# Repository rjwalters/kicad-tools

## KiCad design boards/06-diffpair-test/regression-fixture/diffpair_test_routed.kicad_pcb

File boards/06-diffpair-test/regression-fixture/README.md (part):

> **Current assembled demo (revision C):** four real SN65LVDS1DR / SN65LVDS2DR
> links. See [assembled-demo/README.md](../assembled-demo/README.md) for the circuit,
> procurement and build instructions. `output/` contains that assembly.
> Historical synthetic USB/PCIe/MIPI regression artifacts are retained in
> `regression-fixture/`; the old recipe now defaults to `regression-output/`.
> The historical protocol discussion below describes that regression only.

# Differential Pair Test Board (Board 06)

Regression testbench for the differential-pair routing subsystem introduced
by Epic [#2556](https://github.com/2AMLogic/kicad-tools/issues/2556)
(Phases 1-3).  Demonstrates each protocol family the epic was scoped against
(USB 2.0, USB 3.0, PCIe Gen1, MIPI D-PHY) by routing one or more diff pairs
per protocol on a 4-layer JLCPCB tier-1 stackup.

**This is not a working device.**  The source connectors (USB-C, mini-PCIe
edge, FFC) drive synthetic sink footprints (QFN, QFP, BGA simulator).  The
board's purpose is to exercise every Phase 1-3 net-class feature on at least
one pair so future router/validate changes have an end-to-end witness on
disk.

> **Not native-DRC evidence.** The footprints in this fixture's `*.kicad_pcb`
> files use invented library names (e.g. `Connector_FFC:FFC_4P_0.5mm`,
> `Package_BGA:BGA-49_5.0x5.0mm_Layout7x7_P0.5mm`) that are not in the stock
> KiCad libraries, so pinned kicad-cli DRC reports `lib_footprint_issues` on
> them. This artifact is a router regression witness only and must never be
> committed as native DRC/ERC evidence; the stock-named `../output/` board is
> the evidence artifact. Do not suppress `lib_footprint_issues` to hide this.

## Quick Start

```bash
# One-command build (recommended)
kct build boards/06-diffpair-test

# Or run specific steps
kct build boards/06-diffpair-test --step schematic
kct build boards/06-diffpair-test --step pcb
kct build boards/06-diffpair-test --step route
kct build boards/06-diffpair-test --step verify

# Run DRC against the committed routed PCB
kct check boards/06-diffpair-test/output/diffpair_test_routed.kicad_pcb --mfr jlcpcb
```

## Stackup

4-layer JLCPCB tier-1:

| Layer index | KiCad name | Purpose                              |
|-------------|-----------|--------------------------------------|
| 0           | F.Cu      | Signal (escape + outer routing)      |
| 1           | In1.Cu    | GND plane (impedance reference)      |
| 2           | In2.Cu    | PWR plane (+3V3 / +1V8 / +1V2)       |
| 31          | B.Cu      | Signal (optional bottom escape)      |

This is what the Phase 3K impedance formulas
(`src/kicad_tools/router/diffpair_impedance.py`) were calibrated against.

## Protocol Scenarios

| Scenario   | Pairs | Speed         | Source -> Sink                       | Phase features exercised                                          |
|------------|-------|---------------|--------------------------------------|-------------------------------------------------------------------|
| USB 2.0    | 1     | 480 Mbps      | USB-C (J1) -> QFN-32 (U1)            | 1C clearance, 2E coupled, 2G continuity, 3K 90 Ohm diff           |
| USB 3.0    | 4     | 5 Gbps        | USB-C (J1) -> BGA-49 simulator (U2)  | 1C, 2E, 2F BGA escape, 2G tight (0.9), 3K 90 Ohm, 3H 4.0 ps skew  |
| PCIe Gen1  | 2     | 2.5 Gbps      | Mini-PCIe edge (J3) -> QFP-48 (U3)   | 1C, 2E, 3H 8.1 ps skew, 3I serpentine, 3J skew DRC, 3K 100 Ohm    |
| MIPI D-PHY | 2     | 1 Gbps/lane   | FFC (J4) -> QFN-24 (U4)              | 1C, 2E, 3I serpentine (20.1 ps skew), 3K 100 Ohm                  |

**9 differential pairs / 18 paired nets**.  Combined with ground / power /
single-ended sideband (USB_CC1, USB_CC2, MIPI_RST), the board has **26 nets
total** --- comparable in scale to board 03 (13 nets) and well below
board 05 (~50 nets).

## Components

| Reference | Description                              | Footprint                                          |
|-----------|------------------------------------------|---------------------------------------------------|
| J1        | USB-C receptacle (USB 2.0 + USB 3.0)     | `Connector_USB:USB_C_Receptacle_USB2.0`           |
| J3        | Mini-PCIe card-edge (synthetic)          | `Connector_PCIE:PCIE_Mini_Edge`                   |
| J4        | 4-pin FFC, 0.5 mm pitch                  | `Connector_FFC:FFC_4P_0.5mm`                      |
| U1        | QFN-32, 0.5 mm pitch (USB 2.0 sink)      | `Package_DFN_QFN:QFN-32-1EP_5x5mm_P0.5mm`         |
| U2        | BGA-49 simulator, 0.5 mm pitch           | `Package_BGA:BGA-49_5.0x5.0mm_Layout7x7_P0.5mm`   |
| U3        | QFP-48, 0.5 mm pitch (PCIe sink)         | `Package_QFP:LQFP-48_7x7mm_P0.5mm`                |
| U4        | QFN-24, 0.5 mm pitch (MIPI sink)         | `Package_DFN_QFN:QFN-24-1EP_4x4mm_P0.5mm`         |

All sinks are placed on F.Cu so all routing happens on the outer signal
layers; GND/PWR planes are unencumbered for impedance reference.

## Per-Protocol Net Class Declarations

The protocol-specific `NetClassRouting` instances live in `generate_design.py`:

- `usb2_net_class()` --- `target_diff_impedance=90`, `intra_pair_clearance=0.075`, `pair_protocol="USB2_HS"`
- `usb3_net_class()` --- `target_diff_impedance=90`, `coupled_continuity_threshold=0.9`, `pair_protocol="USB3_SS"`
- `pcie_net_class()` --- `target_diff_impedance=100`, `pair_protocol="PCIE_G1"`
- `mipi_net_class()` --- `target_diff_impedance=100`, `pair_protocol="MIPI_DPHY"`, `data_rate_gbps=1.0`
- `sideband_net_class()` --- `target_single_impedance=50` (for USB_CC1/CC2, MIPI_RST)

No class sets `skew_tolerance_mm` (Issue #7894): every pair is held to the
derived ps skew budget of its declared protocol
([guide 09](../../../docs/guides/diff-pairs/09-skew-budget.md)).  USB 2.0,
USB 3.0 and PCIe Gen1 run at their protocol's maximum rate, so their budgets
are warnings; MIPI declares its 1 Gb/s lane rate, so its 20.1 ps budget is an
error.

`build_net_class_map()` assembles them into a `net_name -> NetClassRouting`
dict that both the autorouter (in `route_pcb()`) and the regression test
(`tests/test_board_06_diffpair_test.py::test_phase_features_exercised`)
import.  This ensures test-implementation parity.

## Files

| File                                          | Description                                          |
|-----------------------------------------------|------------------------------------------------------|
| `project.kct`                                 | KCT v1.0 spec (manufacturing/intent metadata)        |
| `generate_schematic.py`                       | Emits the schematic (`output/diffpair_test.kicad_sch`) |
| `generate_pcb.py`                             | Emits the unrouted PCB + holds the NETS / DIFFPAIRS dicts |
| `generate_design.py`                          | End-to-end pipeline (schematic + PCB + route + DRC)  |
| `output/diffpair_test.kicad_sch`              | Generated schematic (committed)                      |
| `output/diffpair_test.kicad_pcb`              | Unrouted PCB (committed)                             |
| `output/diffpair_test_routed.kicad_pcb`       | Routed PCB (committed --- consumed by CI DRC gate)   |

## DRC Status

The routed PCB is checked against JLCPCB tier-1 rules via:

```bash
kct check output/diffpair_test_routed.kicad_pcb --mfr jlcpcb --errors-only
```

**Phase-3 dependencies**:

- [#2649](https://github.com/2AMLogic/kicad-tools/issues/2649)
  (Phase 3J `diffpair_length_skew` DRC rule) --- **landed** in PR #2662.
  Once the router populates `skew_data`, the rule fires on PCIe / MIPI
  skew violations.
- [#2648](https://github.com/2AMLogic/kicad-tools/issues/2648)
  (Phase 3I serpentine insertion) --- **landed** (closed).  At
  scaffold-time it was still in progress, so PCIe / MIPI pairs could
  exceed their declared `skew_tolerance_mm` because the router couldn't
  yet meander to fix skew.

*Historical scaffold-time context*: per the Epic #2556 Phase 4L
mitigation strategy, this board was scaffolded with PCIe / MIPI pairs
declared but DRC tolerated at "non-strict" while #2648 was pending.
Both dependencies have since landed; the remaining tolerated residual is
the identity-keyed diff-pair quality block documented under "CI Gate"
below.

## Measuring Changes: Regen Determinism (#4536)

Full board-06 regeneration (`generate_design.py --step route`) was
run-to-run nondeterministic downstream of the coupled diff-pair
pre-phase --- two same-seed runs of unmodified `main` could differ by
thousands of lines ([#4536]).  Instrumented run matrices plus a CI-log
bisection localized **three** sources:

1. **Dominant: wall-clock truncation.**  The negotiated stage's
   `timeout=360.0` backstop straddled the phase's own natural runtime
   (363--367 s measured) and fired mid-iteration at a load-dependent net
   boundary in **every** run (different copper counts, 1599--1602
   segments), and any finite stage timeout also keeps the #3989
   remaining-budget per-net wall-clock caps active.  Fixed by removing
   wall-clock control flow from the negotiated stage (`timeout=None`;
   the stage is bounded by its deterministic iteration exits: per-net
   node-expansion budget, memory backstop, `max_iterations=3`,
   best-stall patience, and the #4463 zero-overflow fixed-point exit)
   and pinning `PYTHONHASHSEED=42` by construction at the
   `generate_design.py` entry point (one-shot re-exec), so plain
   invocations no longer depend on the caller exporting it.
   `max_iterations=3` is the *deterministic* replacement for what the
   backstop was doing: in every instrumented run (4 local baselines and
   the green CI run 31214686048) the 360 s cut landed at the very start
   of iteration 4, and iterations 4+ are provably discarded by the
   end-of-loop lex restore, so bounding the count reproduces the
   historical trajectory *and* saves the 9--14 minutes the discarded
   round cost.  Do not raise it back to the default 10 without
   re-measuring --- the board-06 E2E CI job ran to 29m45s of its 30-min
   ceiling with iteration 4 enabled.

2. **Reach-deciding: the relief rescue's 10 s sub-search wall clock.**
   Board-06 reach is decided at negotiated iteration 2 by ONE relief
   rescue (`MIPI_RST`), which rips four MIPI blockers and commits only
   if all four re-land (the no-net-loss transaction guarantee).  Those
   re-lands were bounded by a flat 10 s wall clock that straddles their
   8--12 s natural time on GitHub runners, so the same commit produced
   21/21 on one runner and 20/21 on another from routing logs that are
   line-identical up to the rescue.  Fixed with
   `route_all_negotiated(deterministic_rescue=True)`, which bounds the
   rescue's probe / re-land sub-searches by the deterministic per-net
   node-expansion cap instead.  This board opted in first (#4536) and
   remains an explicit opt-in: #4730 proposed making it the fleet default
   and withdrew the flip on a measured board-07 regression, so
   `DETERMINISTIC_RESCUE_DEFAULT` is `False` on every entry point.  The
   `True` here is therefore not documentary — it is **load-bearing for
   `REQUIRED_SIGNAL_REACH = 21`** in
   `scripts/ci/check_diffpair_coverage.py`.

3. **Residual: UUID-sorted file order.**  With the wall clock removed,
   runs produced byte-identical routing logs and identical copper
   *multisets* yet still ~2300 differing artifact lines.  Stage-snapshot
   comparison across two runs proved every stage through the repair-via
   placement identical, with divergence entering at the first post-repair
   `kct zones fill` --- `kicad-cli` re-saves the board with tracks
   ordered by UUID, and the stitch/pour-repair emitters minted random
   `uuid.uuid4()` values, so each run's refills sorted the *identical*
   copper into a different file order (isolation test: two fills of the
   same file are deterministic; a fill of a byte-equivalent file with
   different UUIDs reorders).  Fixed by minting deterministic UUIDs:
   content-derived uuid5 in `kct stitch` (`_stitch_uuid`) and
   sequence-derived uuid5 in this board's `_generate_uuid`.

**Determinism guard**: `tests/test_board06_determinism.py` runs two
consecutive same-seed shadow-OFF regens and asserts identical segment /
via counts, then byte-identity after normalizing uuid values (and
nothing else --- `kicad-cli` mints random uuid4s for the pads/properties
the generator emits without UUID fields, so raw byte identity can never
hold; all *copper* UUIDs are deterministic after #4536).  It costs two
full regens (~25 min), so it is skipped unless explicitly enabled:

```bash
KCT_BOARD06_DETERMINISM=1 uv run pytest tests/test_board06_determinism.py -v -s
```

**Scope-guard convention** (PR #4526 discussion): "flag-OFF run must
produce a byte-identical committed artifact" is decidable for board-06
again, with two provisos --- compare *uuid-normalized* text, and note
the committed artifact predates the #4536 fix, so regen-vs-committed
diffs remain expected until the artifact is next regenerated; the
run-to-run invariant (regen A vs regen B at the same commit) is the one
the test enforces.  Same-host runs only --- cross-host determinism is
#4561's axis, and shadow-ON determinism remains out of scope.  One more
proviso: run the two regens *sequentially on an otherwise-quiet host*
(the smoke test's own protocol).  Under extreme concurrent load
(measured at load-average ~90: parallel full test suites + mypy on the
same host) one of three post-fix runs flipped a single
stagnation-recovery reroute from success to failure and produced
different (valid) copper --- a resource-exhaustion sensitivity distinct
from the deterministic-logic sources fixed here (filed as #4724 with the
preserved evidence).

**The shadow-construction phase itself is fully deterministic.** This was
established independently more than once during a 5-issue diffpair sweep
(2026-08-03/04, [#4570]/[#4574]/[#4575]/[#4577]/[#4579]/[#4581]/[#4582]):
two full runs at the same commit produce byte-identical sets of all 33
`[coupled-tail]` lines, all 47 `[coupled-follow] declined` lines, and 323
gate rejections from the #4575 via-clearance gate (split 3+15+68+107+82+7+34+7
across the 9 pairs). The #4582 Judge independently reproduced the same
323 figure across four separate runs spanning both downstream modes
below. The nondeterminism is entirely downstream of this phase.

The **decline count is now 46**, not 47 --- [#4604] retired one decline.
Re-confirmed 2026-08-14 under [#4800] at 46 declines / 33 `[coupled-tail]`
lines on two independent runs, so use 46 as the baseline any new
measurement is compared against.

Reproduce the shadow phase and its debug trace:

```bash
KCT_BOARD06_SHADOW=1 PYTHONHASHSEED=42 uv run python \
  boards/06-diffpair-test/generate_design.py --step route --seed 42
# KCT_SHADOW_DEBUG=1 adds the [coupled-tail] / [coupled-follow] instrumentation
```

### The two downstream modes

**All figures in this subsection are from the shadow-ON configuration
(`KCT_BOARD06_SHADOW=1`, the repro block above).  The default recipe
runs shadow-OFF** --- `ENABLE_COUPLED_SHADOW` reads `KCT_BOARD06_SHADOW`
with default `"0"` (`generate_design.py`, the #3508 block), which is what
the committed artifact and CI use.

Once shadow output feeds the negotiated `route_all_negotiated` pass, the
shadow-ON board settles into one of two stable modes rather than a
continuum:

| (shadow-ON) | DRC errors | `diffpair_clearance_intra` | reach |
|---|---|---|---|
| Mode A | 32 | 7 | 19 of 21 |
| Mode B | 35 | 19 | 18 of 21 |

Both [#4800] repeats (2026-08-14, main @ `fa18a25b`) landed in **Mode B**
and were byte-identical to each other modulo `(uuid …)` --- 424 uuid lines
changed, zero geometry lines --- so on the current tree a shadow-ON pair of
runs is not guaranteed to sample both modes.  Sample enough repeats to
*identify* your mode before comparing; do not assume a single run of each
side straddles them.

`coupled-ok` is 5/9 in both modes --- the shadow-ON convergence figure
recorded in the recipe comments ("Convergence is 5/9 (post-#4576)").  A
run's mode is identifiable from three mutually consistent signals ---
total DRC error count, the `diffpair_clearance_intra` count, and reach
--- which is what makes paired mode-for-mode comparison possible instead
of guesswork.

**If you ran with the default (shadow-OFF), you are not in either
mode.** Expect the CI seed-42 re-route instead: **11 blocking DRC
errors**, every one listed by identity in
`DIFFPAIR_FIXTURE_ALLOWED_FINDINGS` (`scripts/ci/check_diffpair_coverage.py`,
#7367: 9 `diffpair_length_skew` pairs, 1 `diffpair_uncoupled_length`,
1 `impedance`), at **21 of 21** reach --- the shadow-OFF reach recorded
in the same recipe comments.  A default-config run landing on those numbers is the expected
result, not an unrecognized third mode.

### Measurement convention

- **Compare shadow-phase counters directly.** The `[coupled-tail]` /
  `[coupled-follow] declined` line counts and the per-pair gate-rejection
  split are deterministic; a difference there is a real signal.
- **Compare full-regen (board-level) results paired mode-for-mode.**
  Identify each side's mode from the three signals above before
  comparing error counts, `diffpair_clearance_intra`, or reach across a
  change.
- **Never assert a delta from a single run of each side.** A lone
  before/after pair can silently compare Mode A against Mode B and
  report a mode flip as a regression or a win. Run enough repeats to
  identify the mode on both sides first.

Two traps this has already cost people:

1. A Builder's first baseline landed in Mode A while the Curator's had
   landed in Mode B, so the two disagreed on the "current" numbers and
   neither was wrong.
2. A Builder ran a narrow-vs-broad comparison that looked decisive and
   was pure mode noise --- only paired sampling separated signal from
   [#4536].

### Standing invariants and the vacuity trap

A change should not drop `coupled-ok` below 5/9, and should not drop
reach when compared mode-for-mode.  **The 5/9 figure is the shadow-ON
convergence number** recorded in the recipe comments next to
`ENABLE_COUPLED_SHADOW`; like the mode table, it is an invariant for
shadow-ON runs, so evaluate it against a shadow-ON baseline rather than
a default (shadow-OFF) one.  Watch for the **vacuity trap**:
`diffpair_length_skew` only fires on an *engaged* (coupled) pair, so a
change that knocks a pair from coupled to declined removes it from
skew-checking entirely --- the error count can drop while the change is
a regression, not a win.  Always read `coupled-ok` and reach alongside
the raw error count, never the error count alone.

### Why the default is shadow-OFF (measured, [#4800], 2026-08-14)

The obvious question --- "5/9 coupled beats 0/9, why is this off?" --- has
a measured answer.  Two repeats per arm on main @ `fa18a25b`
(`PYTHONHASHSEED=42 … --seed 42`, C++ backend built), board quality read
with the CI gate itself (`scripts/ci/check_diffpair_coverage.py
--skip-route`) and cross-checked with `kicad-cli pcb drc --refill-zones`:

| | shadow OFF (default) | shadow ON |
|---|---|---|
| `coupled-ok` | 0/9 | 5/9 |
| `[coupled-follow] declined` | n/a | 46 |
| signal reach | **21/21** | **18/21** |
| `kct check` DRC errors | **18** (allowlist 18) | **35** |
| diff-pair violations | 18 (baseline 18) | 31 |
| pour connectivity | PASS | **FAIL** (+3V3 3 groups, GND 5 groups) |
| `kicad-cli` errors | 444 (11 clearance) | 639–646 (169–176 clearance) |
| `kicad-cli` unconnected | 0 | **9** |
| `--step route` wall-clock | 745.2 s / 739.9 s | 1649.8 s / 1570.6 s |
| CI gate exit code | **0** | **2** (4 assertions) |

The 5 pairs that couple are stable by name --- MIPI_CLK, PCIE_RX, USB2_D,
USB3_TX1, USB3_TX2.  The three stranded nets are MIPI_D0+, MIPI_D0- and
USB_CC1; the [#4463] corridor-yield recovery yields MIPI_CLK, re-runs,
measures `reach 18 -> 18 of 21` and **reverts**, so shadow-ON no longer
reaches the 19/21 recorded on 2026-08-02.  USB_CC1 is still not a
corridor-competition failure --- the planner says so itself:
`[corridor-yield] USB_CC1 stays unroutable with every coupled corridor
lifted`.  Wall-clock is 2.16x, against a CI job already running a median
24.5 min of its 30-minute ceiling (ten consecutive green main runs,
2026-08-14; the re-route step alone is 23m30s).

### The crossover legality census (`KCT_CROSSTAIL_CENSUS=1`)

The shadow constructor's crossover tails ship the **first** legal via-site
candidate out of a 225-entry lattice and report nothing about the rest, so an
*ordering* problem (many sites legal, a better key would pick a kinder one)
looks exactly like a *saturation* one (almost nothing is legal, so no key can
help).  `KCT_CROSSTAIL_CENSUS=1` ([#4580]) scans the whole lattice instead and
prints one header per crossover:

```bash
KCT_CROSSTAIL_CENSUS=1 KCT_BOARD06_SHADOW=1 PYTHONHASHSEED=42 uv run python \
  boards/06-diffpair-test/generate_design.py --step route --seed 42
# [crosstail-census] net=… head=(…) goal=(…) legal=2/225 distinct_v1=1 census_s=0.0164
```

`distinct_v1` is the field that separates the two worlds: a legal set that is a
singleton in `v1` carries the same barrel on every legal route, so no ordering
key can move the result and the constraint lives upstream in placement / escape
planning.

Add `KCT_CROSSTAIL_CENSUS_REPORT=<path>`
([#4799](https://github.com/2AMLogic/kicad-tools/issues/4799)) to get the same measurement
as **data** instead of scraped stdout: a JSON document with one record per
crossover plus the aggregate the per-crossover headers cannot give you
(`saturated_pct`, `no_ordering_lever_pct`, `inert_pct`, an advisory `verdict`).
The diff-pair phase also closes with a `[crosstail-census-summary]` block
whenever the census is on.  It is report-only and costs ~1 µs per crossover on
top of the census itself; schema and interpretation live in
[`docs/reference/crosstail-census-report.md`](../../../docs/reference/crosstail-census-report.md).

That report is a post-mortem, but it does not have to be read as one: feeding
it back in with `kct route --census-advisory <report.json>` (or
`KCT_CROSSTAIL_CENSUS_ADVISORY=<path>`) prints this board's saturation figure
**before** the next route's first A\* expansion, cross-checked against the
board's current nets and suppressed when the report is stale.  Advisory by
default — it cannot change or fail a route.  Adding `--census-advisory-gate`
(opt-in) turns that prediction into a go/no-go: on this board's own report it
exits **9** before any router work rather than spending the 28 minutes again,
naming the worst nets and pointing at placement / escape planning as the fix
layer.  A prediction that cannot be trusted (stale, `not-applicable`,
census-disabled) never gates.

**State-neutral is not the same as budget-neutral ([#4635]).** PR [#4611]'s
prose claimed the census "cannot" change the route because it is
"observation-only by construction".  That is true of router **state** — every
gate the scan calls past the accept point is mutation-free, so continuing the
sweep cannot perturb anything.  It was **not** true of the wall-clock
**budget**: the census runs inside the shadow phase's per-pair window, and every
downstream deadline there is computed as `<budget> - <elapsed since the window
opened>`, so census seconds were silently deducted from the probes that follow.
A census-on run could therefore differ from a census-off run through budget
pressure alone.  Since #4635 the census credits its own **incremental** cost
(the sweep after the first legal candidate — zero when nothing is legal, since
both modes then scan the whole lattice) back to that window, so census-on and
census-off runs get the same effective downstream budget.  The trade is
deliberate: a census-on pair's *true* wall clock may now exceed the 30 s
`_SHADOW_PER_PAIR_BUDGET_S` by the census's own cost, which stays visible in
`census_s=` and in the unadjusted per-pair `[coupled-timing] elapsed=` line.

**Measured on this board** (shadow-ON, seed 42, 2026-08-04 — re-measure before
quoting): 166 crossovers, of which **150 (90.4%) have `legal=0/225`** and so
credit exactly zero.  Total credited census time across the whole shadow phase
is **1.28 s**; the worst single pair (USB3_TX1) accrues **0.86 s**, i.e. under
3% of its 30 s budget.  That is a **refutation** of the budget-pressure
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
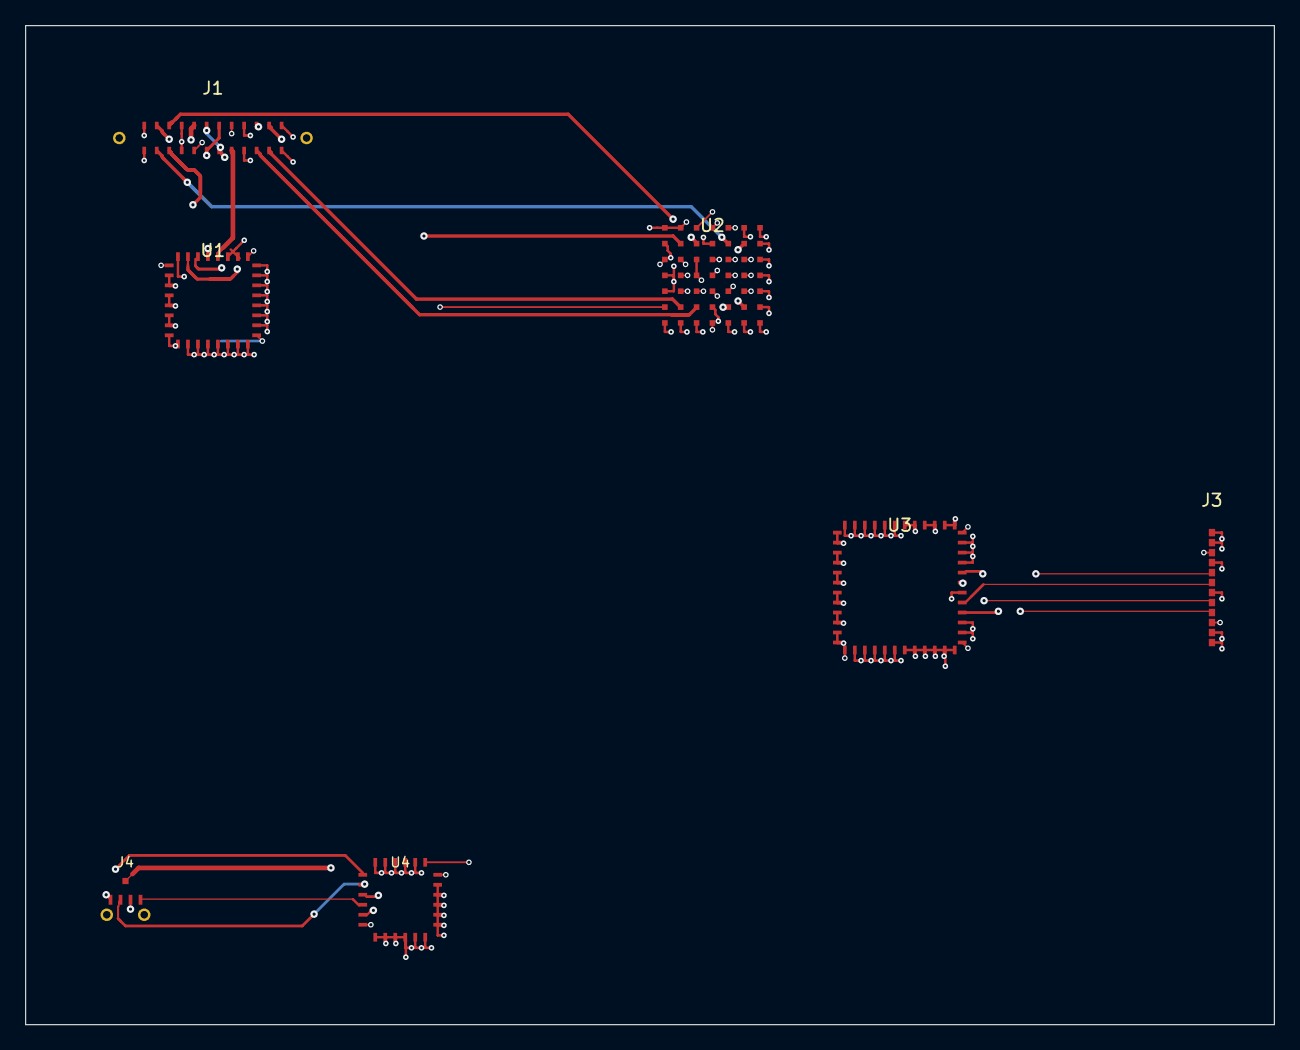
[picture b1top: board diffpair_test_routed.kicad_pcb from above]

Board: 4 copper layers, 100.0 x 80.0 mm, 7 parts (0 on the bottom side), 26 nets.

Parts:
J1: USB-C; USB_C_Receptacle_USB2.0
J3: MiniPCIe; PCIE_Mini_Edge
J4: FFC4; FFC_4P_0.5mm
U1: QFN32_USB2; QFN-32-1EP_5x5mm_P0.5mm
U2: BGA49_USB3; BGA-49_5.0x5.0mm_Layout7x7_P0.5mm
U3: QFP48_PCIe; LQFP-48_7x7mm_P0.5mm
U4: QFN24_MIPI; QFN-24-1EP_4x4mm_P0.5mm

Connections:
+1V2: J3.10, U2.C3, U2.C4, U2.C5, U2.D2, U2.D3, U2.D4, U2.D5, U2.D6, U2.E3, U2.E4, U2.E5, U3.36
+1V8: U1.16, U4.6, U4.18
+3V3: J1.A8, J1.B8, J3.3, U1.1, U1.17, U2.C2, U2.C6, U2.E2, U2.E6, U3.25, U4.12
GND: J1.A1, J1.A12, J1.B1, J1.B12, J1.S1, J1.S2, J3.1, J3.2, J3.4, J3.7, J3.11, J3.12, J4.M1, J4.M2, U1.2, U1.3, U1.4, U1.5, U1.6, U1.7, U1.8, U1.14, U1.15, U1.18, U1.19, U1.20, U1.21, U1.22, U1.23, U1.24, U1.25, U1.26, U1.27, U1.28, U1.29, U1.30, U1.31, U1.32, U2.A1, U2.A2, U2.A3, U2.A4, U2.A5, U2.A6, U2.A7, U2.B1, U2.B4, U2.B7, U2.C1, U2.C7, U2.D1, U2.D7, U2.E1, U2.E7, U2.F1, U2.F4, U2.F7, U2.G1, U2.G2, U2.G3, U2.G4, U2.G5, U2.G6, U2.G7, U3.1, U3.2, U3.3, U3.4, U3.5, U3.6, U3.7, U3.8, U3.9, U3.10, U3.11, U3.12, U3.13, U3.14, U3.15, U3.16, U3.17, U3.18, U3.19, U3.20, U3.21, U3.22, U3.23, U3.24, U3.26, U3.27, U3.30, U3.33, U3.34, U3.35, U3.37, U3.38, U3.39, U3.40, U3.41, U3.42, U3.43, U3.44, U3.45, U3.46, U3.47, U3.48, U4.7, U4.8, U4.9, U4.10, U4.11, U4.13, U4.14, U4.15, U4.16, U4.17, U4.19, U4.20, U4.21, U4.22, U4.23, U4.24
MIPI_CLK+: J4.1, U4.1
MIPI_CLK-: J4.2, U4.2
MIPI_D0+: J4.3, U4.3
MIPI_D0-: J4.4, U4.4
MIPI_RST: J4.RST, U4.5
PCIE_RX+: J3.8, U3.31
PCIE_RX-: J3.9, U3.32
PCIE_TX+: J3.5, U3.28
PCIE_TX-: J3.6, U3.29
USB2_D+: J1.A6, J1.B6, U1.10
USB2_D-: J1.A7, J1.B7, U1.11
USB3_RX1+: J1.B11, U2.B5
USB3_RX1-: J1.B10, U2.B6
USB3_RX2+: J1.A11, U2.F5
USB3_RX2-: J1.A10, U2.F6
USB3_TX1+: J1.A2, U2.B2
USB3_TX1-: J1.A3, U2.B3
USB3_TX2+: J1.B2, U2.F2
USB3_TX2-: J1.B3, U2.F3
USB_CC1: J1.A5, U1.12
USB_CC2: J1.B5, U1.13
VBUS_USB: J1.A4, J1.A9, J1.B4, J1.B9, U1.9

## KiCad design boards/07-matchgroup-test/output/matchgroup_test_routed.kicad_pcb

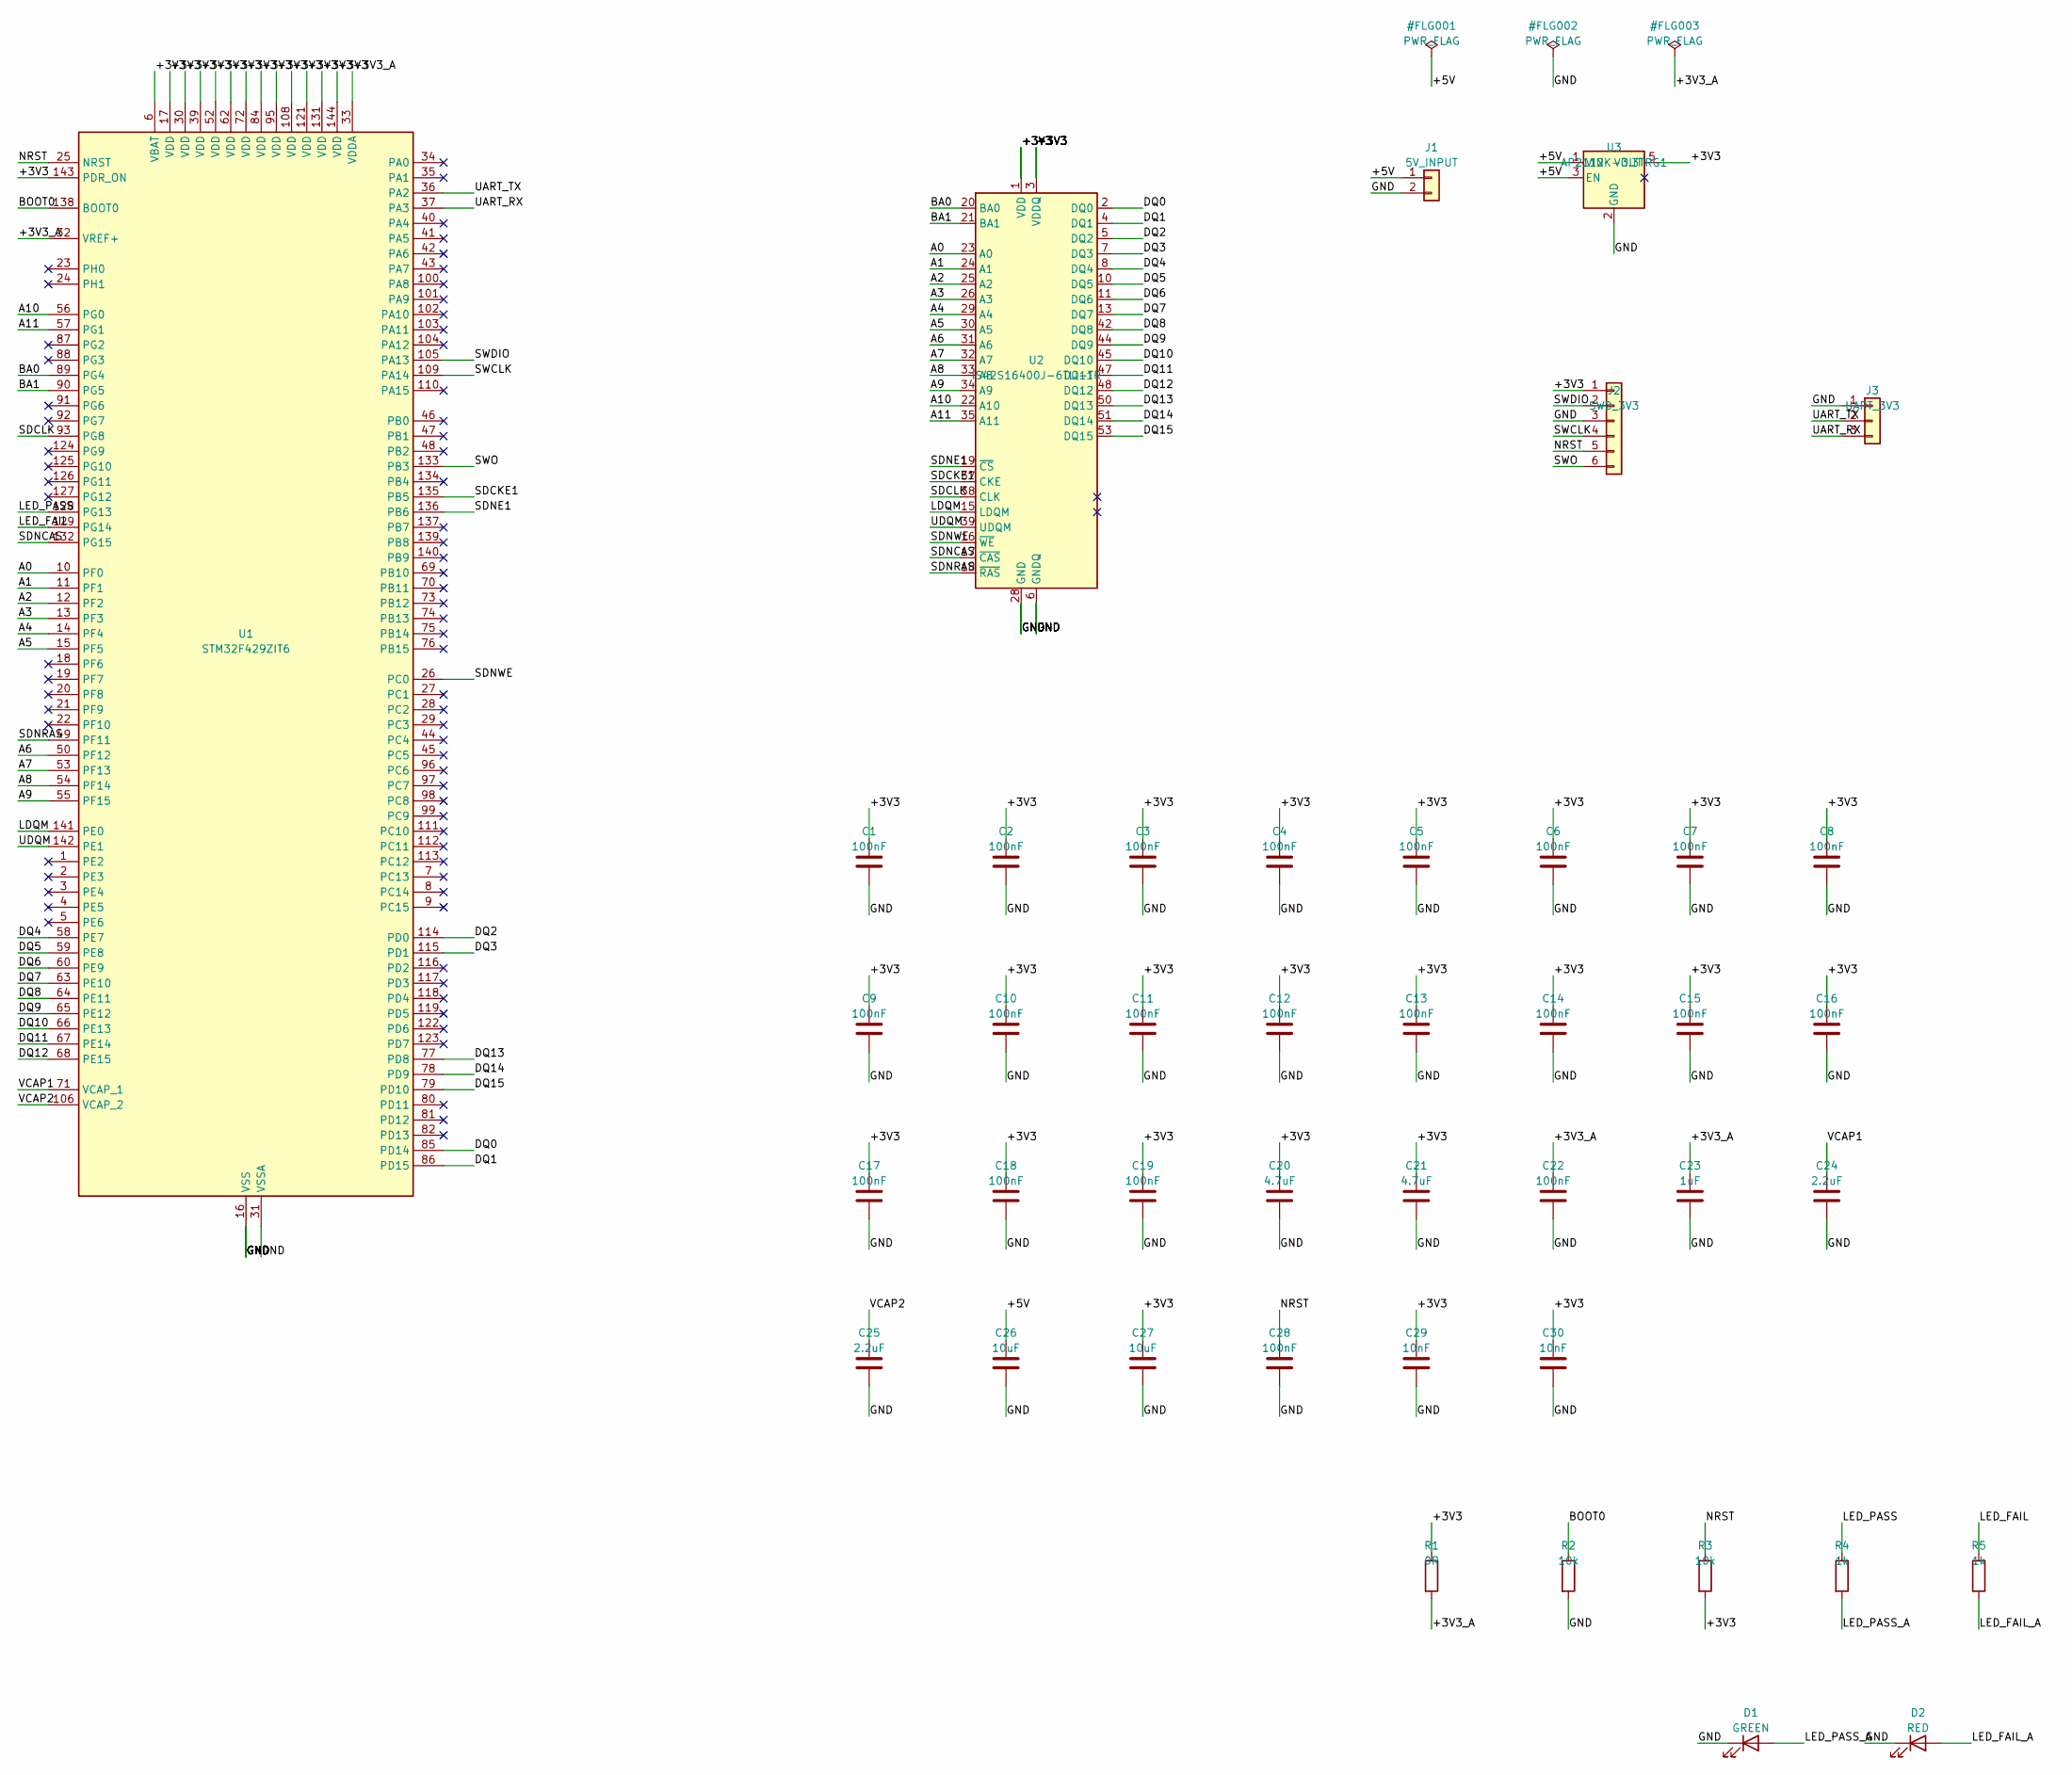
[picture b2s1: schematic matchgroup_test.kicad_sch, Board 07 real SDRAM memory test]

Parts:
C1, C2, C3, C4, C5, C6, C7, C8, C9, C10, C11, C12, C13, C14, C15, C16, C17, C18, C19, C22, C28: 100nF; C_0603_1608Metric; Manufacturer_Part_Number CC0603KRX7R9BB104; LCSC C14663
C20, C21: 4.7uF; C_0603_1608Metric; Manufacturer_Part_Number CL10A475KP8NNNC; LCSC C1705
C23: 1uF; C_0603_1608Metric; Manufacturer_Part_Number CL10A105KB8NNNC; LCSC C15849
C24, C25: 2.2uF; C_0603_1608Metric; Manufacturer_Part_Number CL10A225KO8NNNC; LCSC C23630
C26, C27: 10uF; C_0603_1608Metric; Manufacturer_Part_Number CL10A106KP8NNNC; LCSC C19702
C29, C30: 10nF; C_0603_1608Metric; Manufacturer_Part_Number CL10B103KB8NNNC; LCSC C1589
D1: GREEN; LED_0603_1608Metric; Manufacturer_Part_Number LTST-C190KGKT; LCSC C125094
D2: RED; LED_0603_1608Metric; Manufacturer_Part_Number LTST-C190KRKT; LCSC C94869
J1: 5V_INPUT; PinHeader_1x02_P2.54mm_Vertical; Manufacturer_Part_Number B-2100S02P-A110; LCSC C124375
J2: SWD_3V3; PinHeader_1x06_P2.54mm_Vertical; Manufacturer_Part_Number 2.54-1x6P; LCSC C37208
J3: UART_3V3; PinHeader_1x03_P2.54mm_Vertical; Manufacturer_Part_Number 2.54-1*3P; LCSC C49257
R1: 0R; R_0603_1608Metric; Manufacturer_Part_Number 0603WAF0000T5E; LCSC C21189
R2, R3: 10k; R_0603_1608Metric; Manufacturer_Part_Number 0603WAF1002T5E; LCSC C25804
R4, R5: 1k; R_0603_1608Metric; Manufacturer_Part_Number 0603WAF1001T5E; LCSC C21190
U1: STM32F429ZIT6; LQFP-144_20x20mm_P0.5mm; Manufacturer_Part_Number STM32F429ZIT6; LCSC C84808
U2: IS42S16400J-6TLI-TR; TSOP-II-54_22.2x10.16mm_P0.8mm; Manufacturer_Part_Number IS42S16400J-6TLI-TR; LCSC C17216754
U3: AP2112K-3.3TRG1; SOT-23-5; Manufacturer_Part_Number AP2112K-3.3TRG1; LCSC C51118

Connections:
+3V3: C1.1, C2.1, C3.1, C4.1, C5.1, C6.1, C7.1, C8.1, C9.1, C10.1, C11.1, C12.1, C13.1, C14.1, C15.1, C16.1, C17.1, C18.1, C19.1, C20.1, C21.1, C27.1, C29.1, C30.1, J2.1, R1.1, R3.2, U1.6 (VBAT), U1.17 (VDD), U1.30 (VDD), U1.39 (VDD), U1.52 (VDD), U1.62 (VDD), U1.72 (VDD), U1.84 (VDD), U1.95 (VDD), U1.108 (VDD), U1.121 (VDD), U1.131 (VDD), U1.143 (PDR_ON), U1.144 (VDD), U2.1 (VDD), U2.3 (VDDQ), U2.9 (VDDQ), U2.14 (VDD), U2.27 (VDD), U2.43 (VDDQ), U2.49 (VDDQ), U3.5 (VOUT)
+3V3_A: C22.1, C23.1, R1.2, U1.32 (VREF+), U1.33 (VDDA)
+5V: C26.1, J1.1, U3.1 (VIN), U3.3 (EN)
A0: U1.10 (PF0), U2.23 (A0)
A1: U1.11 (PF1), U2.24 (A1)
A2: U1.12 (PF2), U2.25 (A2)
A3: U1.13 (PF3), U2.26 (A3)
A4: U1.14 (PF4), U2.29 (A4)
A5: U1.15 (PF5), U2.30 (A5)
A6: U1.50 (PF12), U2.31 (A6)
A7: U1.53 (PF13), U2.32 (A7)
A8: U1.54 (PF14), U2.33 (A8)
A9: U1.55 (PF15), U2.34 (A9)
A10: U1.56 (PG0), U2.22 (A10)
A11: U1.57 (PG1), U2.35 (A11)
BA0: U1.89 (PG4), U2.20 (BA0)
BA1: U1.90 (PG5), U2.21 (BA1)
BOOT0: R2.1, U1.138 (BOOT0)
DQ0: U1.85 (PD14), U2.2 (DQ0)
DQ1: U1.86 (PD15), U2.4 (DQ1)
DQ2: U1.114 (PD0), U2.5 (DQ2)
DQ3: U1.115 (PD1), U2.7 (DQ3)
DQ4: U1.58 (PE7), U2.8 (DQ4)
DQ5: U1.59 (PE8), U2.10 (DQ5)
DQ6: U1.60 (PE9), U2.11 (DQ6)
DQ7: U1.63 (PE10), U2.13 (DQ7)
DQ8: U1.64 (PE11), U2.42 (DQ8)
DQ9: U1.65 (PE12), U2.44 (DQ9)
DQ10: U1.66 (PE13), U2.45 (DQ10)
DQ11: U1.67 (PE14), U2.47 (DQ11)
DQ12: U1.68 (PE15), U2.48 (DQ12)
DQ13: U1.77 (PD8), U2.50 (DQ13)
DQ14: U1.78 (PD9), U2.51 (DQ14)
DQ15: U1.79 (PD10), U2.53 (DQ15)
GND: C1.2, C2.2, C3.2, C4.2, C5.2, C6.2, C7.2, C8.2, C9.2, C10.2, C11.2, C12.2, C13.2, C14.2, C15.2, C16.2, C17.2, C18.2, C19.2, C20.2, C21.2, C22.2, C23.2, C24.2, C25.2, C26.2, C27.2, C28.2, C29.2, C30.2, D1.1 (K), D2.1 (K), J1.2, J2.3, J3.1, R2.2, U1.16 (VSS), U1.31 (VSSA), U1.38 (VSS), U1.51 (VSS), U1.61 (VSS), U1.83 (VSS), U1.94 (VSS), U1.107 (VSS), U1.120 (VSS), U1.130 (VSS), U2.6 (GNDQ), U2.12 (GNDQ), U2.28 (GND), U2.41 (GND), U2.46 (GNDQ), U2.52 (GNDQ), U2.54 (GND), U3.2 (GND)
LDQM: U1.141 (PE0), U2.15 (LDQM)
LED_FAIL: R5.1, U1.129 (PG14)
LED_FAIL_A: D2.2 (A), R5.2
LED_PASS: R4.1, U1.128 (PG13)
LED_PASS_A: D1.2 (A), R4.2
NRST: C28.1, J2.5, R3.1, U1.25 (NRST)
SDCKE1: U1.135 (PB5), U2.37 (CKE)
SDCLK: U1.93 (PG8), U2.38 (CLK)
SDNCAS: U1.132 (PG15), U2.17 (~CAS)
SDNE1: U1.136 (PB6), U2.19 (~CS)
SDNRAS: U1.49 (PF11), U2.18 (~RAS)
SDNWE: U1.26 (PC0), U2.16 (~WE)
SWCLK: J2.4, U1.109 (PA14)
SWDIO: J2.2, U1.105 (PA13)
SWO: J2.6, U1.133 (PB3)
UART_RX: J3.3, U1.37 (PA3)
UART_TX: J3.2, U1.36 (PA2)
UDQM: U1.142 (PE1), U2.39 (UDQM)
VCAP1: C24.1, U1.71 (VCAP_1)
VCAP2: C25.1, U1.106 (VCAP_2)

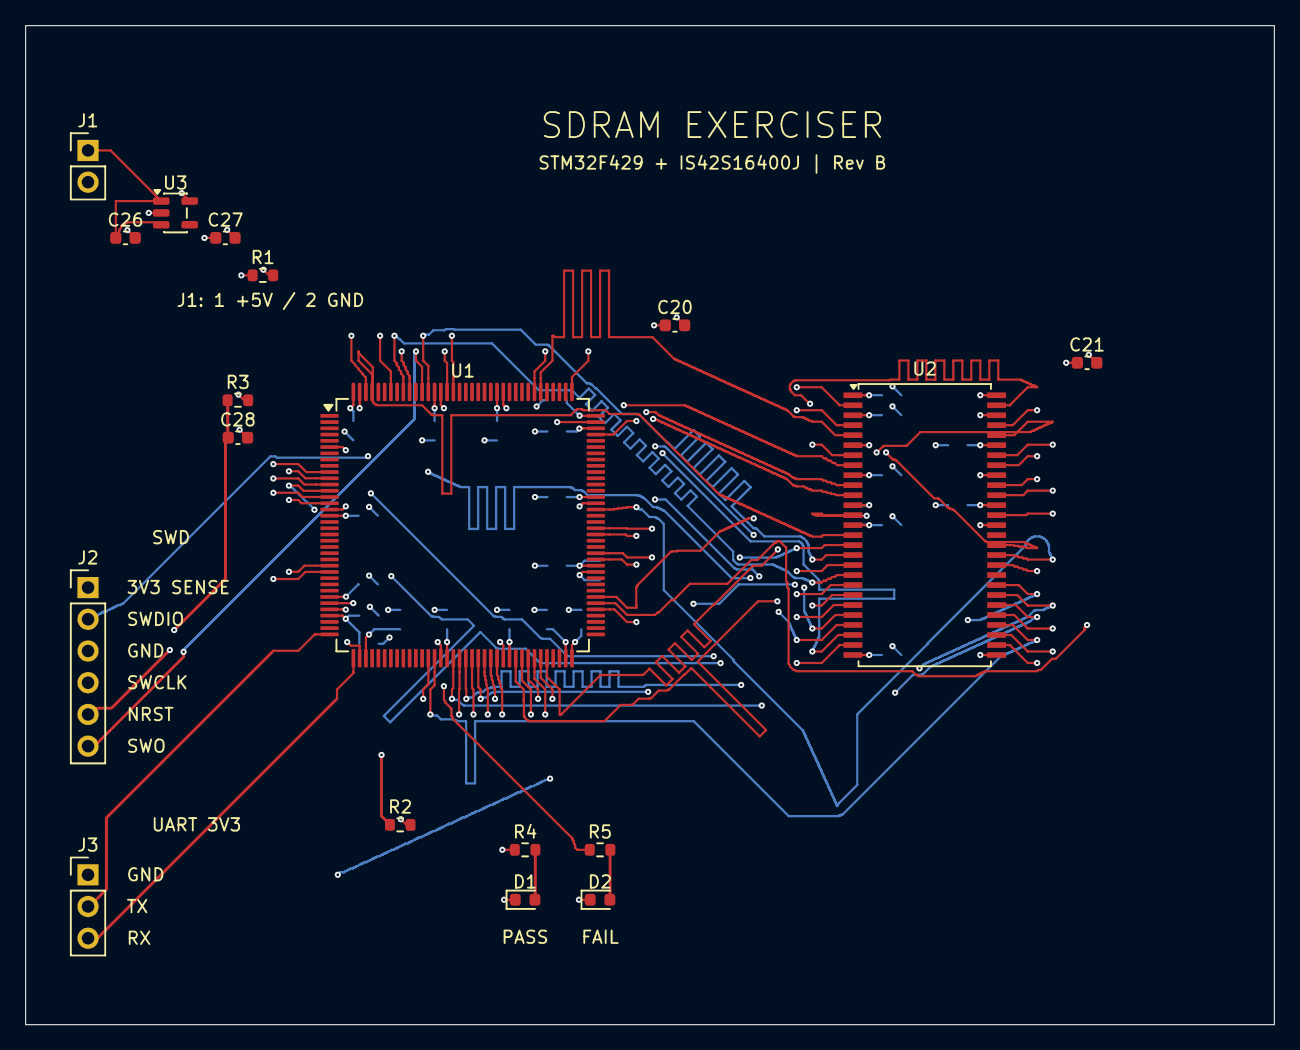
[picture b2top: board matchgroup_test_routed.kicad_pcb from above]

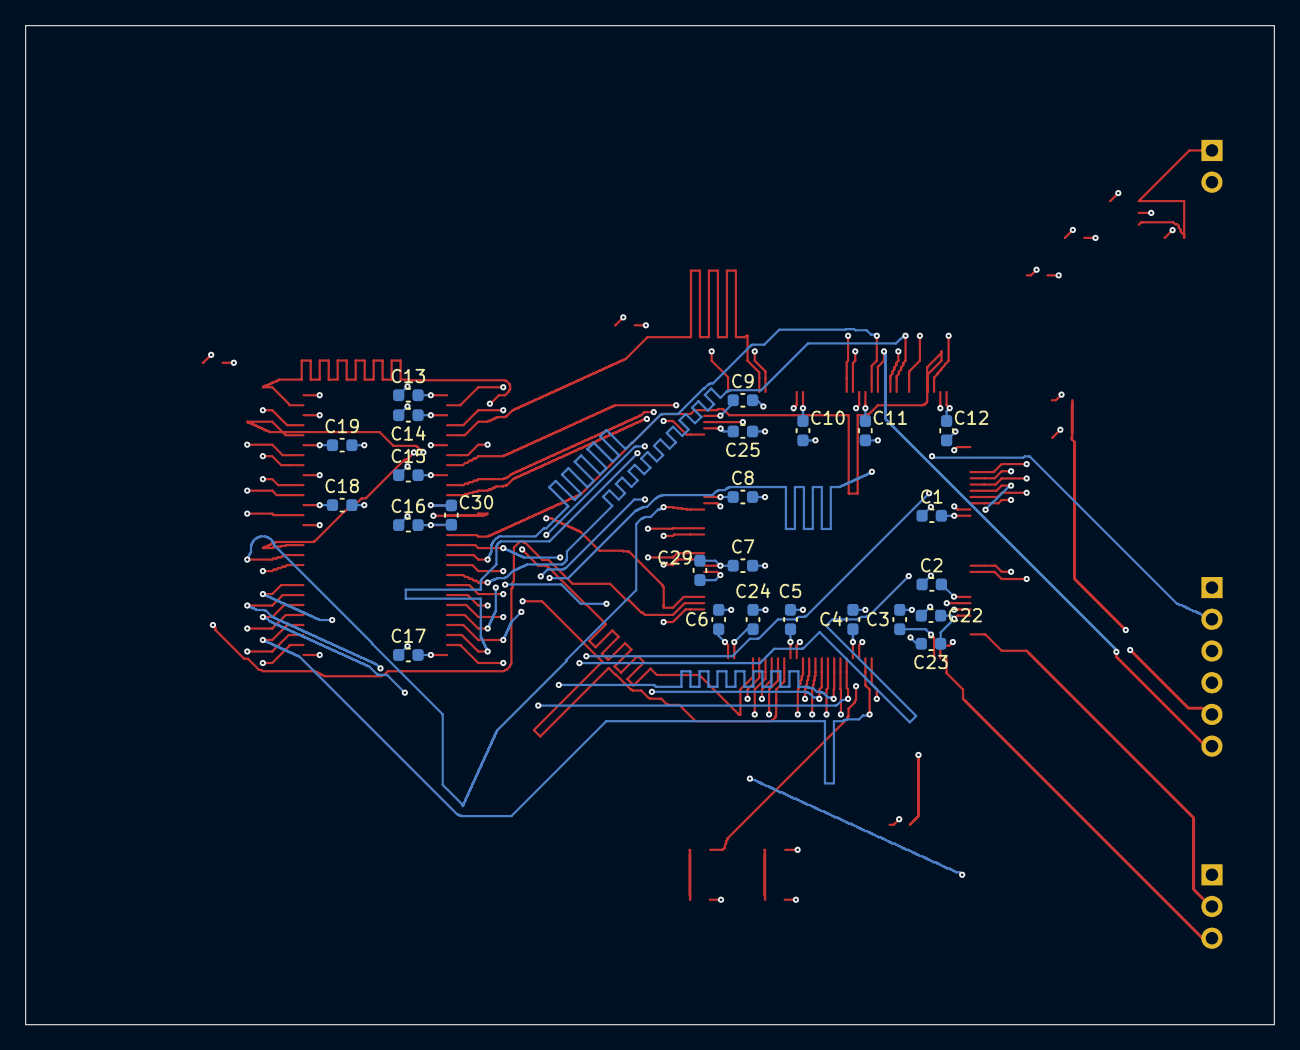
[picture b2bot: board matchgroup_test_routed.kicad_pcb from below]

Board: 6 copper layers, 100.0 x 80.0 mm, 43 parts (25 on the bottom side), 55 nets.

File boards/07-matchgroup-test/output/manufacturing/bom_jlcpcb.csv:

Comment,Designator,Footprint,LCSC Part #
0R,R1,Resistor_SMD:R_0603_1608Metric,C21189
100nF,"C1,C10,C11,C12,C13,C14,C15,C16,C17,C18,C19,C2,C22,C28,C3,C4,C5,C6,C7,C8,C9",Capacitor_SMD:C_0603_1608Metric,C14663
10k,"R2,R3",Resistor_SMD:R_0603_1608Metric,C25804
10nF,"C29,C30",Capacitor_SMD:C_0603_1608Metric,C1589
10uF,"C26,C27",Capacitor_SMD:C_0603_1608Metric,C19702
1k,"R4,R5",Resistor_SMD:R_0603_1608Metric,C21190
1uF,C23,Capacitor_SMD:C_0603_1608Metric,C15849
2.2uF,"C24,C25",Capacitor_SMD:C_0603_1608Metric,C23630
4.7uF,"C20,C21",Capacitor_SMD:C_0603_1608Metric,C1705
5V_INPUT,J1,Connector_PinHeader_2.54mm:PinHeader_1x02_P2.54mm_Vertical,C124375
AP2112K-3.3TRG1,U3,Package_TO_SOT_SMD:SOT-23-5,C51118
GREEN,D1,LED_SMD:LED_0603_1608Metric,C125094
IS42S16400J-6TLI-TR,U2,Package_SO:TSOP-II-54_22.2x10.16mm_P0.8mm,C17216754
RED,D2,LED_SMD:LED_0603_1608Metric,C94869
STM32F429ZIT6,U1,Package_QFP:LQFP-144_20x20mm_P0.5mm,C84808
SWD_3V3,J2,Connector_PinHeader_2.54mm:PinHeader_1x06_P2.54mm_Vertical,C37208
UART_3V3,J3,Connector_PinHeader_2.54mm:PinHeader_1x03_P2.54mm_Vertical,C49257

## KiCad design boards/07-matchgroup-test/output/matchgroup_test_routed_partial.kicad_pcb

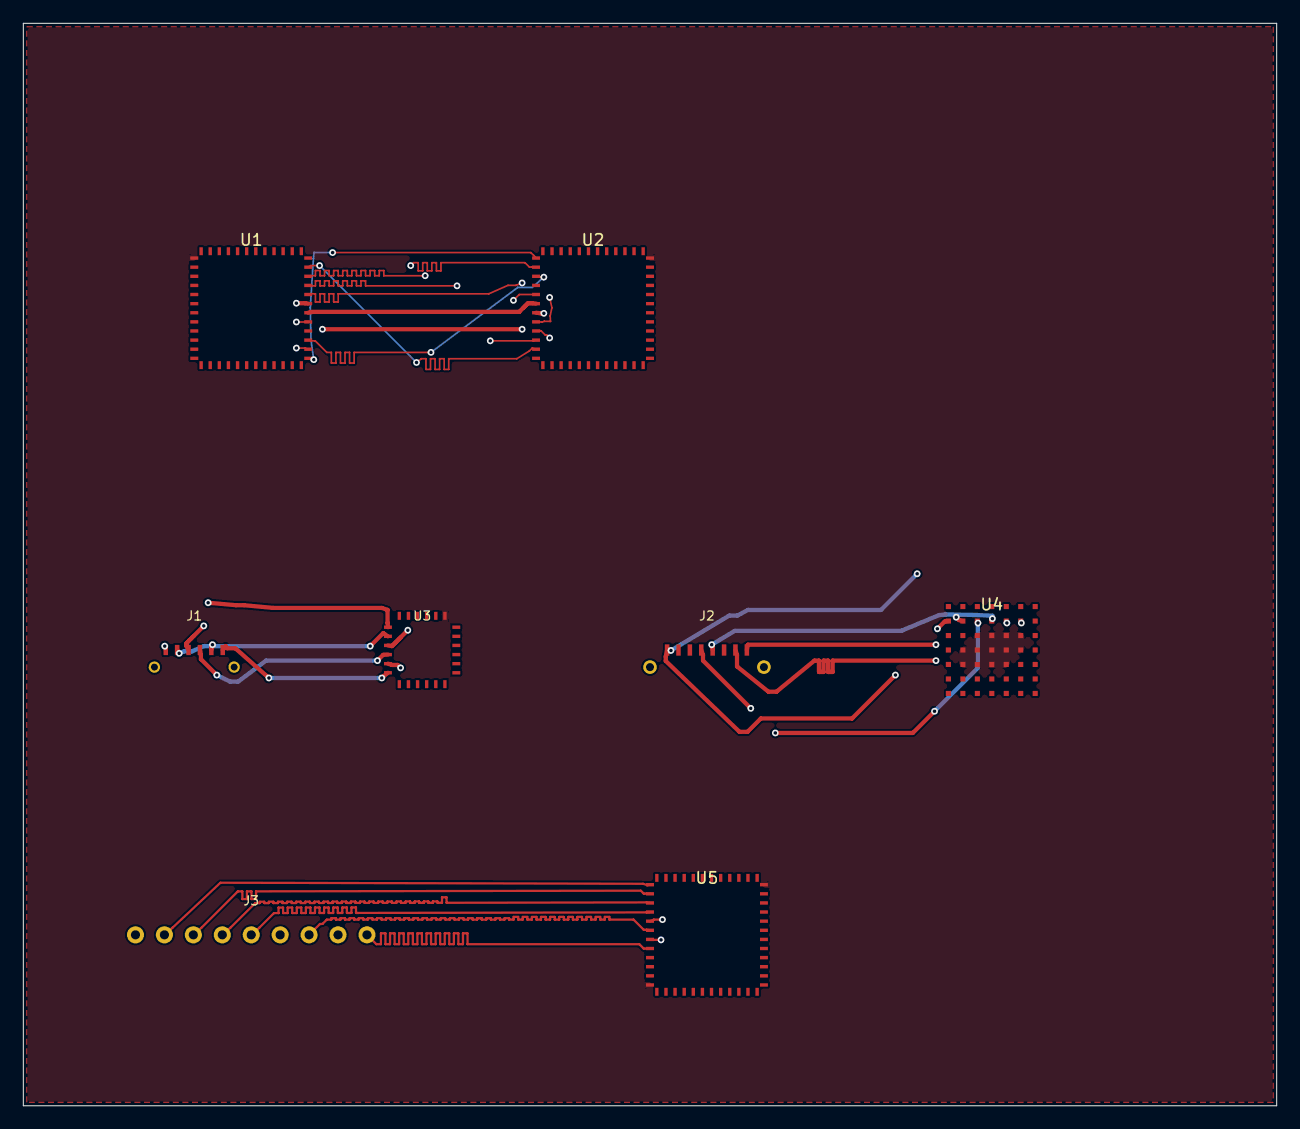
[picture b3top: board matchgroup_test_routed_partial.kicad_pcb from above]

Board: 4 copper layers, 110.0 x 95.0 mm, 8 parts (0 on the bottom side), 34 nets.

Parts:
J1: FFC6_MIPI; FFC_6P_1.0mm
J2: HDMI19; HDMI_A_Receptacle
J3: ADDR_HDR; PinHeader_1x09_P2.54mm_Vertical
U1: QFN48_DDR_CTRL; QFN-48-1EP_7x7mm_P0.5mm
U2: QFN48_DRAM; QFN-48-1EP_7x7mm_P0.5mm
U3: QFN24_MIPI; QFN-24-1EP_4x4mm_P0.5mm
U4: BGA49_HDMI; BGA-49_5.0x5.0mm_Layout7x7_P0.5mm
U5: QFP48_SRAM; LQFP-48_7x7mm_P0.5mm

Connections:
+1V2: U1.12, U1.36, U2.12, U2.24, U3.18, U4.C2, U4.E6, U5.24
+1V8: U1.1, U2.36, U3.12, U4.C3, U4.C4, U4.C5, U4.C6, U4.D2, U4.D3, U4.D4, U4.D5, U4.D6, U4.E2, U4.E3, U4.E4, U4.E5, U5.12, U5.36
A0: J3.2, U5.1
A1: J3.3, U5.2
A2: J3.4, U5.3
A3: J3.5, U5.4
A4: J3.6, U5.5
A5: J3.7, U5.6
A6: J3.8, U5.7
A7: J3.9, U5.8
DM0: U1.29, U2.5
DQ0: U1.25, U2.1
DQ1: U1.26, U2.2
DQ2: U1.27, U2.3
DQ3: U1.28, U2.4
DQ4: U1.32, U2.8
DQ5: U1.33, U2.9
DQ6: U1.34, U2.10
DQ7: U1.35, U2.11
DQS_N: U1.31, U2.7
DQS_P: U1.30, U2.6
GND: J1.M1, J1.M2, J2.3, J2.6, J2.S1, J2.S2, J3.1, U1.2, U1.3, U1.4, U1.5, U1.6, U1.7, U1.8, U1.9, U1.10, U1.11, U1.13, U1.14, U1.15, U1.16, U1.17, U1.18, U1.19, U1.20, U1.21, U1.22, U1.23, U1.24, U1.37, U1.38, U1.39, U1.40, U1.41, U1.42, U1.43, U1.44, U1.45, U1.46, U1.47, U1.48, U2.13, U2.14, U2.15, U2.16, U2.17, U2.18, U2.19, U2.20, U2.21, U2.22, U2.23, U2.25, U2.26, U2.27, U2.28, U2.29, U2.30, U2.31, U2.32, U2.33, U2.34, U2.35, U2.37, U2.38, U2.39, U2.40, U2.41, U2.42, U2.43, U2.44, U2.45, U2.46, U2.47, U2.48, U3.7, U3.8, U3.9, U3.10, U3.11, U3.13, U3.14, U3.15, U3.16, U3.17, U3.19, U3.20, U3.21, U3.22, U3.23, U3.24, U4.A1, U4.A2, U4.A3, U4.A4, U4.A5, U4.A6, U4.A7, U4.B7, U4.C1, U4.C7, U4.D1, U4.D7, U4.E1, U4.E7, U4.F1, U4.F2, U4.F3, U4.F4, U4.F5, U4.F6, U4.F7, U4.G1, U4.G2, U4.G3, U4.G4, U4.G5, U4.G6, U4.G7, U5.9, U5.10, U5.11, U5.13, U5.14, U5.15, U5.16, U5.17, U5.18, U5.19, U5.20, U5.21, U5.22, U5.23, U5.25, U5.26, U5.27, U5.28, U5.29, U5.30, U5.31, U5.32, U5.33, U5.34, U5.35, U5.37, U5.38, U5.39, U5.40, U5.41, U5.42, U5.43, U5.44, U5.45, U5.46, U5.47, U5.48
MIPI_CLK_N: J1.2, U3.2
MIPI_CLK_P: J1.1, U3.1
MIPI_DAT0_N: J1.4, U3.4
MIPI_DAT0_P: J1.3, U3.3
MIPI_DAT1_N: J1.6, U3.6
MIPI_DAT1_P: J1.5, U3.5
TMDS_D0_N: J2.2, U4.B2
TMDS_D0_P: J2.1, U4.B1
TMDS_D1_N: J2.5, U4.B4
TMDS_D1_P: J2.4, U4.B3
TMDS_D2_N: J2.8, U4.B6
TMDS_D2_P: J2.7, U4.B5
